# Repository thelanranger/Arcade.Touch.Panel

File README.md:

# Arcade.Touch.Panel
Capacative Touch Panel using custom PCB and Arduino Leo

int pins are mapped to custom PCB in eagle files. 
Buttons are VCClite capacative touch LCD buttons:
https://vcclite.com/product/csms15cic04/

I specifically used White which did not need SMD resistors and run fine off of USB power (though they are VERY bright).

LEDTimer = 100000;  Can be adjusted to set how long until 'latched' buttons auto off their lights. Example: If you press a button and it is set to 'non latching' the light would blink on touch, but then be in 'always off'. If it was 'latched' (such as mute) the light will remain lit once pressed until it is pressed again OR until LEDTimer ms have passed. Any lights in the 'latched' state would return to their state position on the next button touch.

switch (Bindex) defines the 8 buttons. This sends keystrokes to the system as if the Leonardo was a simple keyboard. The sample file is setup with hotkeys that map to the associated AutoHotKey file to perform the designated actions. 

Example of unlatched press (case 0):
    3 keys are pressed in sequence using Keyboard.press(); then all released using Keyboard.releaseAll();. The light is 'blinked' with a pin write HIGH, delay, and pin write LOW. This sends the sequence of keys then blinks the light. No data is retained and everything is ready for the next loop.

Example of a latched press (case 1):
    lastLEDState[Bindex] is verified. If 'unlatched state' is stored for this button number then we perform the keypress and switch the state from 0 to 1. An immediate exit will allow the cycleLEDs() routine to update turn on the LED and return for the next press. If the reverse is true we can pass the same set of keys again, or an alternate set (in this case we're passing Play [CTRL+SHIFT+G], on latch, then Stop [CTRL+SHIFT+D] on unlatch) and changing the state to off.

This should allow you to perform almost any task! You can even double your buttons with a latching 'shift' button! Just update your .ahk file to match your keystrokes and go nuts.

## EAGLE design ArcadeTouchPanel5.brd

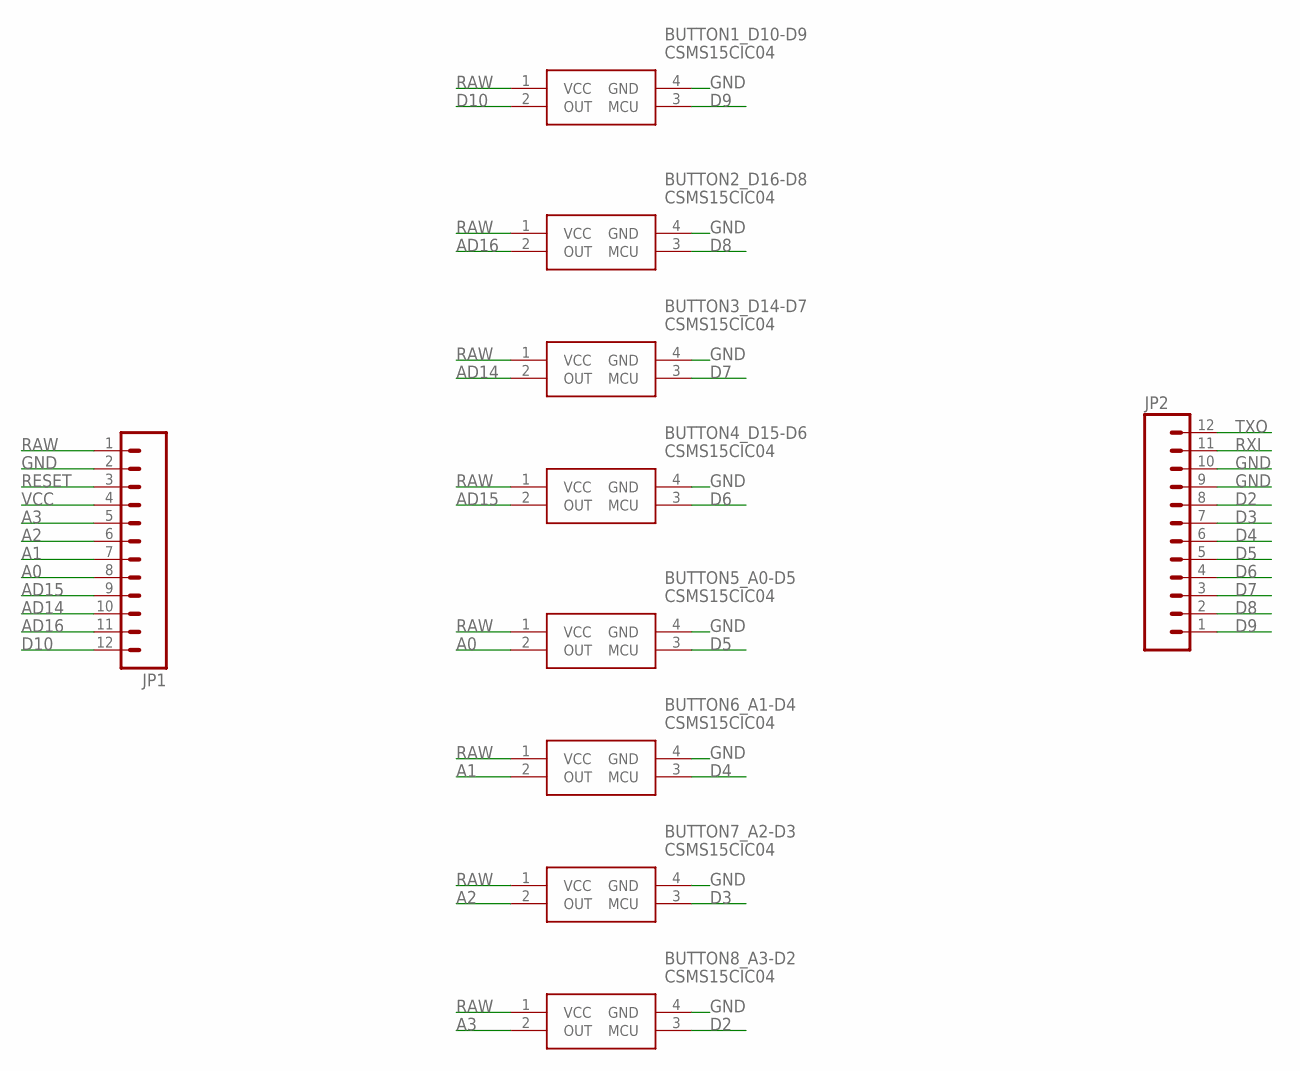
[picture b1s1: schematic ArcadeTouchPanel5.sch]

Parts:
BUTTON1_D10-D9, BUTTON2_D16-D8, BUTTON3_D14-D7, BUTTON4_D15-D6, BUTTON5_A0-D5, BUTTON6_A1-D4, BUTTON7_A2-D3, BUTTON8_A3-D2: CSMS15CIC04
JP1, JP2: M12PTH; 1X12

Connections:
A0: BUTTON5_A0-D5.2 (OUT), JP1.8
A1: BUTTON6_A1-D4.2 (OUT), JP1.7
A2: BUTTON7_A2-D3.2 (OUT), JP1.6
A3: BUTTON8_A3-D2.2 (OUT), JP1.5
AD14: BUTTON3_D14-D7.2 (OUT), JP1.10
AD15: BUTTON4_D15-D6.2 (OUT), JP1.9
AD16: BUTTON2_D16-D8.2 (OUT), JP1.11
D2: BUTTON8_A3-D2.3 (MCU), JP2.8
D3: BUTTON7_A2-D3.3 (MCU), JP2.7
D4: BUTTON6_A1-D4.3 (MCU), JP2.6
D5: BUTTON5_A0-D5.3 (MCU), JP2.5
D6: BUTTON4_D15-D6.3 (MCU), JP2.4
D7: BUTTON3_D14-D7.3 (MCU), JP2.3
D8: BUTTON2_D16-D8.3 (MCU), JP2.2
D9: BUTTON1_D10-D9.3 (MCU), JP2.1
D10: BUTTON1_D10-D9.2 (OUT), JP1.12
GND: BUTTON1_D10-D9.4 (GND), BUTTON2_D16-D8.4 (GND), BUTTON3_D14-D7.4 (GND), BUTTON4_D15-D6.4 (GND), BUTTON5_A0-D5.4 (GND), BUTTON6_A1-D4.4 (GND), BUTTON7_A2-D3.4 (GND), BUTTON8_A3-D2.4 (GND), JP1.2, JP2.9, JP2.10
RAW: BUTTON1_D10-D9.1 (VCC), BUTTON2_D16-D8.1 (VCC), BUTTON3_D14-D7.1 (VCC), BUTTON4_D15-D6.1 (VCC), BUTTON5_A0-D5.1 (VCC), BUTTON6_A1-D4.1 (VCC), BUTTON7_A2-D3.1 (VCC), BUTTON8_A3-D2.1 (VCC), JP1.1
RESET: JP1.3
RXI: JP2.11
TXO: JP2.12
VCC: JP1.4

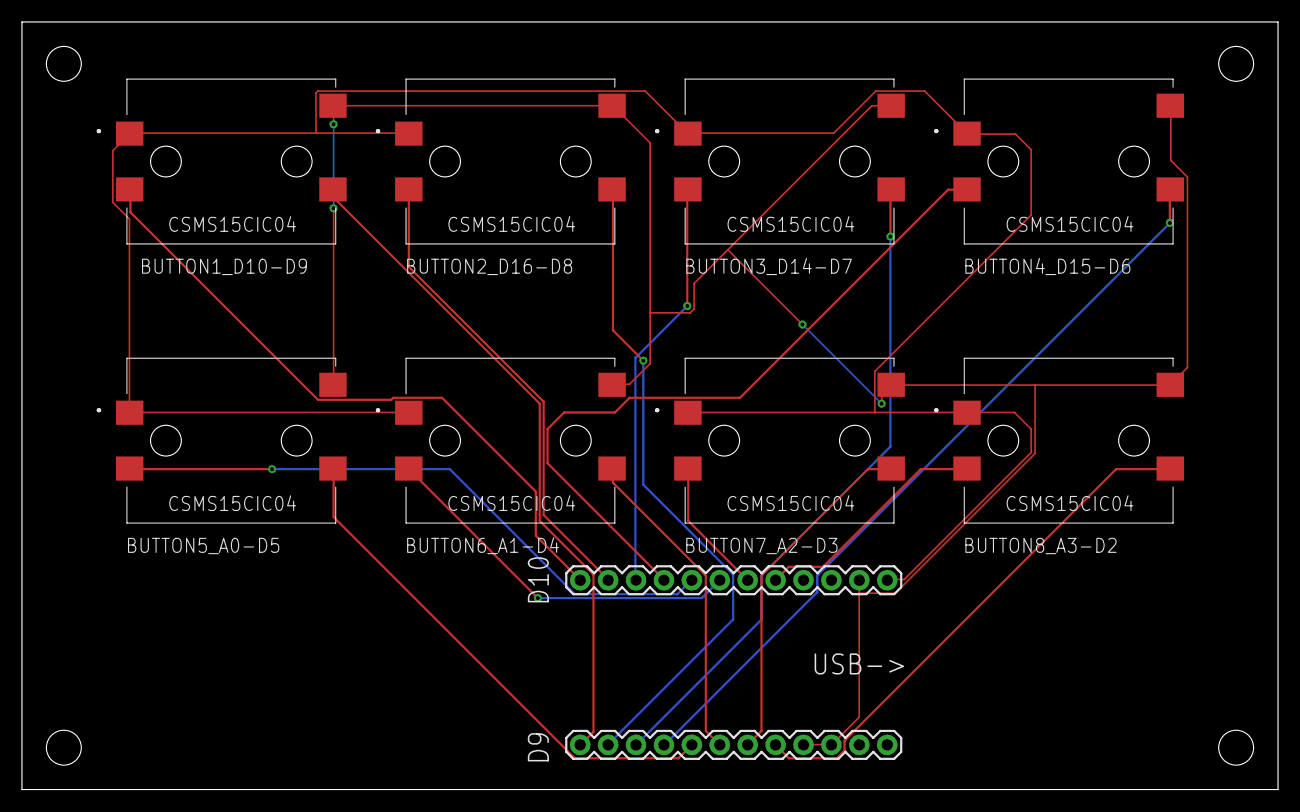
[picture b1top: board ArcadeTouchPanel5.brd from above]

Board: 2 copper layers, 114.3 x 69.8 mm, 10 parts (0 on the bottom side), 18 nets.

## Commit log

2022-10-19 Add files via upload
    Eagle Files for board.
2022-10-19 Add files via upload
    CNC files to send for complete board
